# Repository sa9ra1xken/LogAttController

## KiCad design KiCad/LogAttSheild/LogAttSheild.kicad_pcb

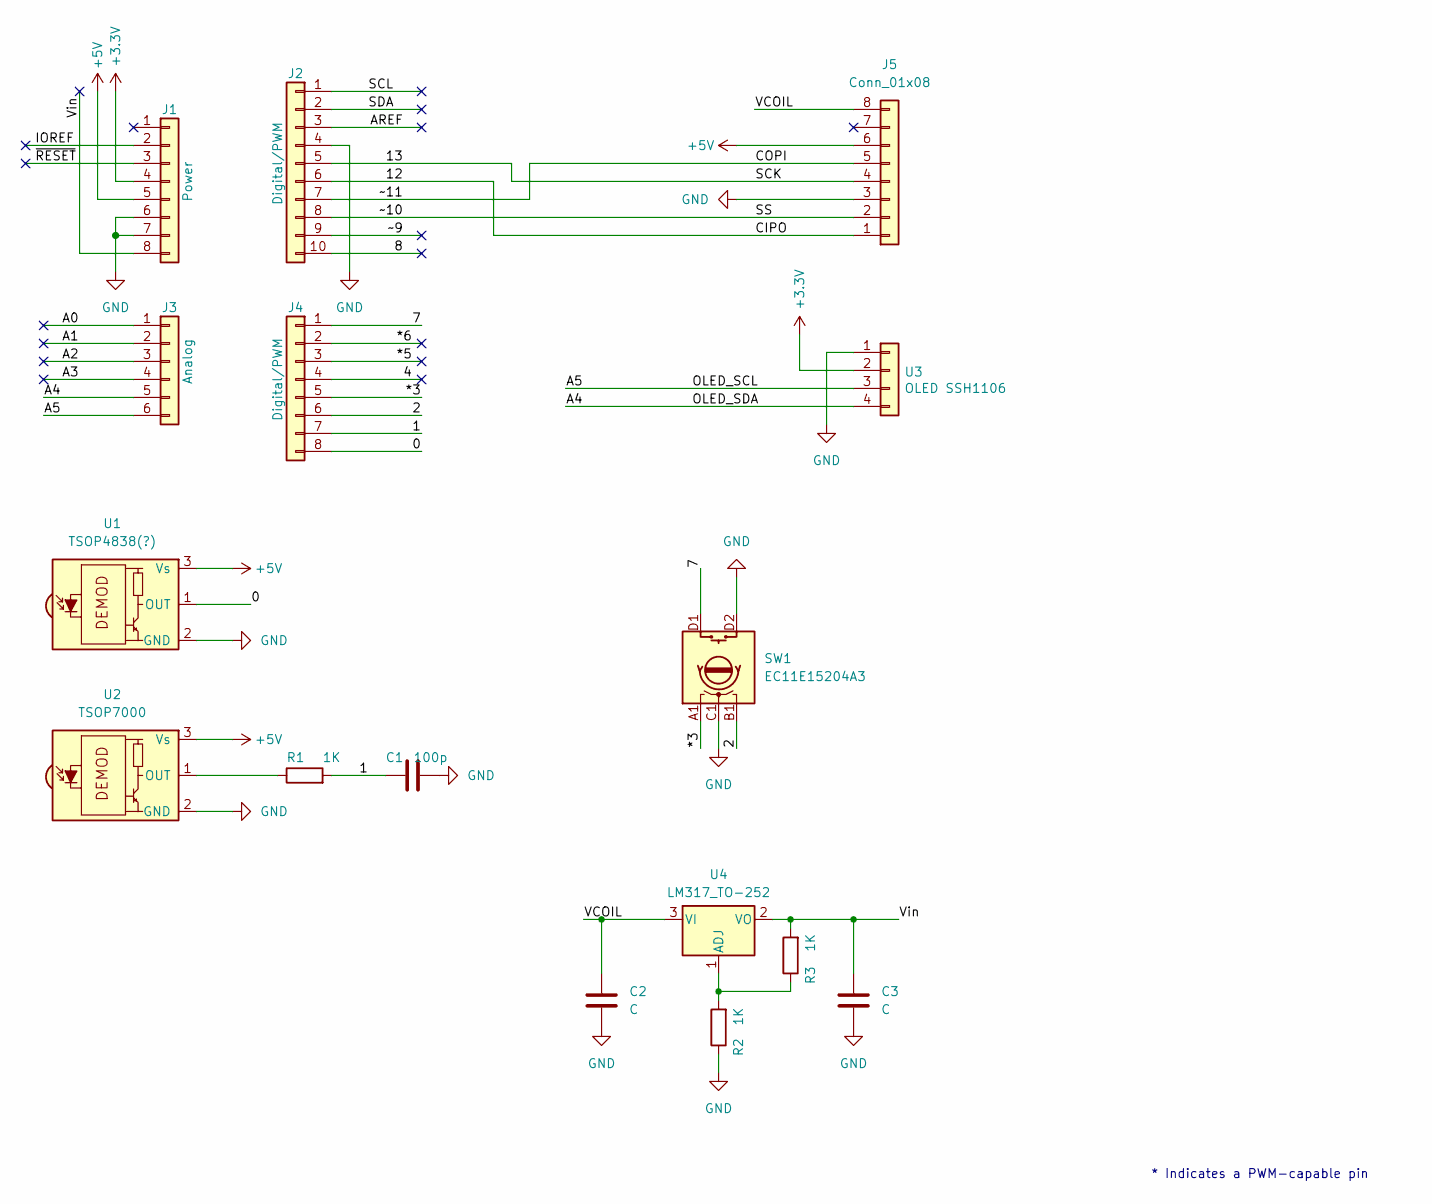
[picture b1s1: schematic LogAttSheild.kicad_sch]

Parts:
C1: 100p; C_0603_1608Metric_Pad1.08x0.95mm_HandSolder
C2, C3: C; C_1206_3216Metric_Pad1.33x1.80mm_HandSolder
J1: Power; PinSocket_1x08_P2.54mm_Vertical
J2: Digital/PWM; PinSocket_1x10_P2.54mm_Vertical
J3: Analog; PinSocket_1x06_P2.54mm_Vertical
J4: Digital/PWM; PinSocket_1x08_P2.54mm_Vertical
J5: Conn_01x08; PinSocket_1x08_P2.54mm_Vertical
R1, R2, R3: 1K; R_0603_1608Metric_Pad0.98x0.95mm_HandSolder
SW1: EC11E15204A3
U1: TSOP4838(?); Vishay_MOLD-3Pin Folded
U2: TSOP7000; Vishay_MOLD-3Pin Folded
U3: OLED SSH1106; OLED_4pin_1.3_128X64
U4: LM317_TO-252; TO-252-2

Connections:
+3.3V: J1.4, U3.2
+5V: J1.5, J5.6, U1.3 (Vs), U2.3 (Vs)
/0: J4.8, U1.1 (OUT)
/1: C1.1, J4.7, R1.2
/2: J4.6, SW1.B1 (B)
/4: J4.4
/7: J4.1, SW1.D1 (S1)
/8: J2.10
/12: J2.6, J5.1
/13: J2.5, J5.4
/*3: J4.5, SW1.A1 (A)
/*5: J4.3
/*6: J4.2
/A0: J3.1
/A1: J3.2
/A2: J3.3
/A3: J3.4
/A4: J3.5, U3.4
/A5: J3.6, U3.3
/AREF: J2.3
/COPI: J2.7, J5.5
/IOREF: J1.2
/SCL: J2.1
/SDA: J2.2
/SS: J2.8, J5.2
/VCOIL: C2.1, J5.8, U4.3 (VI)
/Vin: C3.1, J1.8, R3.2, U4.2 (VO)
/~9: J2.9
/~RESET: J1.3
GND: C1.2, C2.2, C3.2, J1.6, J1.7, J2.4, J5.3, R2.1, SW1.C1 (C), SW1.D2 (S2), U1.2 (GND), U2.2 (GND), U3.1
unnamed: R1.1, U2.1 (OUT)
unnamed: R2.2, R3.1, U4.1 (ADJ)

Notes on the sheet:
* Indicates a PWM-capable pin

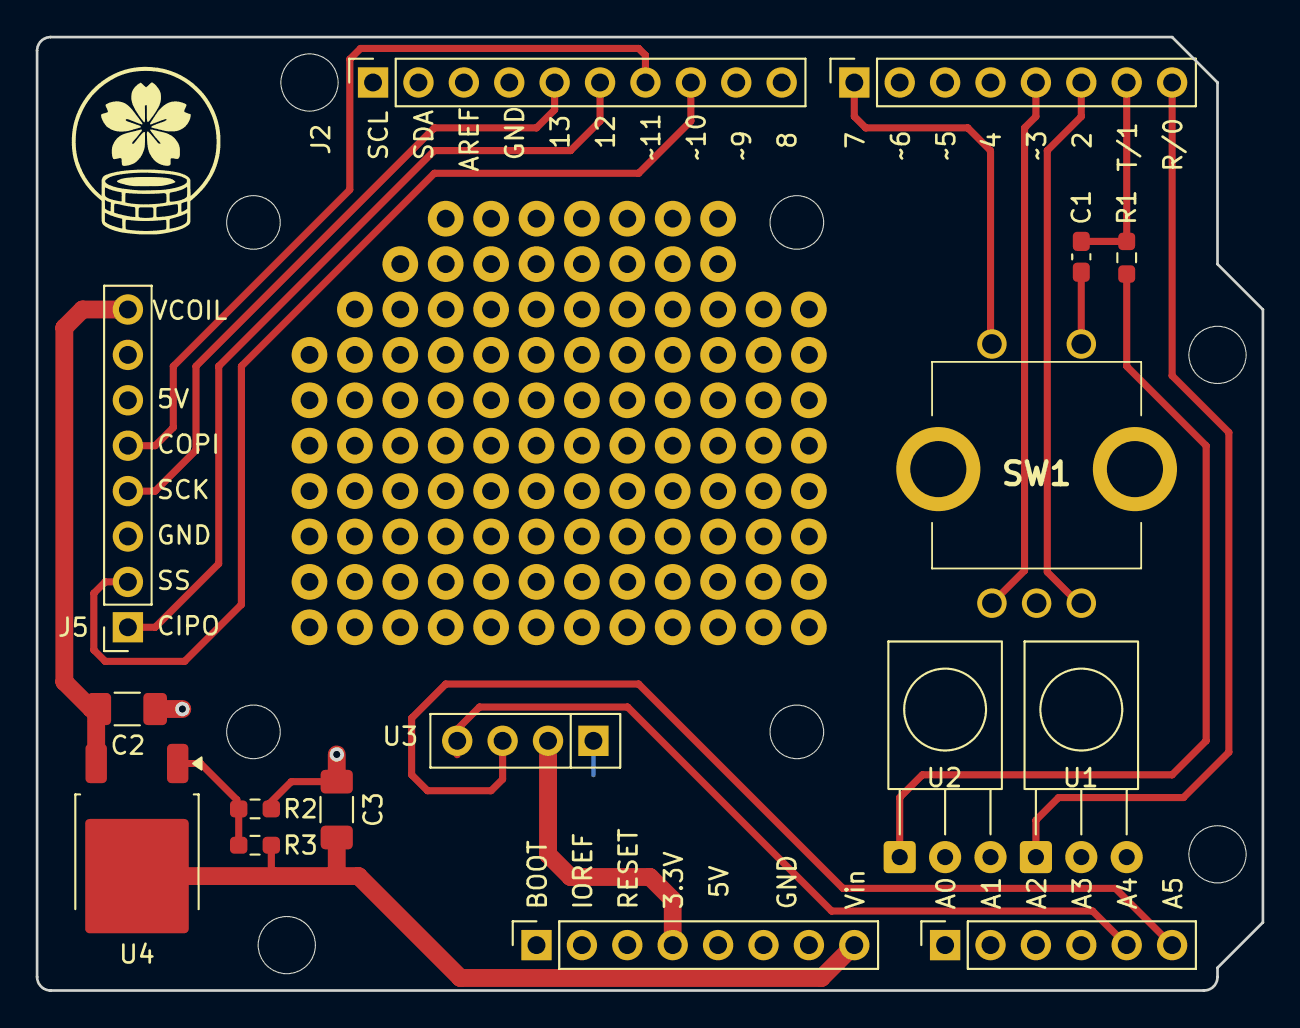
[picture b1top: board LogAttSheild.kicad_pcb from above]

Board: 2 copper layers, 68.6 x 53.3 mm, 20 parts (0 on the bottom side), 18 nets.

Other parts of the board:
MH1, MH2, MH3, MH4: MountingHole_3.2mm

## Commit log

2025-08-17 initial
2025-08-17 uploaded a video.
2025-09-07 first working version
2025-09-08 schematic pdf added
2025-09-09 remote measurement again
2025-09-10 measure with terminator
2025-09-10 spreadsheet saved with LibraOffice
2025-09-11 measurement after re-solder
2025-09-15 refresh
2025-09-25 add F35B
2025-10-03 IR remote control
2025-10-06 refine IR command handring
2025-10-06 add remote control video
2025-10-07 disable IR protocpl except NEC
2025-10-17 測定フォルダ更新。
2025-11-01 pcba design comp
2025-11-01 Gerber generated.
2025-11-06 3D image added.
2026-01-11 Console class implemented.
2026-01-15 Redrawn to apply modular design
